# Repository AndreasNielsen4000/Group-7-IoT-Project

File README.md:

# Group 7 IoT Project: Wireless Stereo Speaker System
This one of the two github pages for Group 7s project for DTU course 34346 Networking technologies and application development for the Internet of Things (IoT).
## Group Members
- Andreas Nielsen: s203833
- Alexander Nordentoft: s176361
- Rasmus Kurdahl-Martinsen: s194337
- Sergio Piqueras Moreno: s232104
- Hugo Velasco Bombin: s233845
- Anton Per Rønnedal: s203821

## Project Description

The project is a wireless speaker system that can play music from a Bluetooth or WiFi source. The system consists of four main parts with subcomponents:

1. A speaker with an ESP32-WROOM-32 microcontroller.
   1. Two custom PCBs
      1. A power board with USB-C PD and a battery management system.
      2. An audio board with a class D amplifier, a DAC, ESP32-WROOM-32, and an nRF24L01 module.
      3. Rotary encoder for volume control and switching modes.
      4. OLED display for showing the current mode, metadata, battery level and volume.
2. ESP32 IoT Bridge
   1. An ESP32-WROOM-32 microcontroller.
   2. nRF24L01 module.
3. Azure Backend
    1. WebAPI for managing the speaker system.
    2. Simple front end for controlling the speaker system.
4. Thunkable App
    1. An app for controlling the speaker system using the Azure backend.

## Description of the Speaker System

*Code in BT_I2S_URL_OLED*

The speaker system consists of a speaker with an ESP32-WROOM-32 microcontroller. The speaker is powered by a custom power board with USB-C PD and a battery management system. The speaker can be powered by three 18650 batteries or by USB-C PD. The battery can be charged using USB-C PD.

The audio is played by a custom audio board with a class D amplifier.

The speaker can play music from a Bluetooth or WiFi source. The speaker can be controlled using the Thunkable app, the Azure backend or by using the rotary encoder and OLED display on the speaker.

When powering on the speaker, a byte will be read form the EEPROM to determine the mode of the speaker. The speaker can be in one of the following modes besides being powered off:
WiFi, Bluetooth, Standby or Charge

When powered on, a short press on the rotary encoder will switch betweent the current active mode to the valid passive mode, e.g. if the speaker is in WiFi mode and charging, a short press will switch to Charge mode. A short press again will switch back to WiFi mode. If the device is not charging, the speaker will go into Standby mode instead. From Standby mode, a long press (10 seconds) will turn off the speaker.

In all modes except powered off, the speaker will show the battery level on the OLED display as well as the current mode. It will have an active nRF network to the IoT Bridge and will be able to receive and transmit payloads from the nRF network.

Once a second the speaker checks for any changes in local device parameters and if they are different from the last time the speaker will send a payload to the IoT Bridge with the new parameters. Should the speaker receive a payload from the IoT Bridge, it will parse the payload and act accordingly.

When in WiFi mode, the speaker will start by playing Radio BOB! bby default. The speaker will show the current song and Internet Radio station on the OLED display.

When in Bluetooth mode, the speaker will connect to the last connected Bluetooth device and that device will be able to play music on the speaker. The speaker will show the current song on the OLED display. When connected to a compatible device, the speaker will show the current song on the OLED display and turning the volume down to 0 sends a pause command to the device. Turning the volume up will send a play command to the device.

When in Standby mode, the speaker will not play music, but the ESP32 will still be running with the OLED display and the nRF network active.

When in Charge mode, the speaker will charge the battery and show the battery level on the OLED display.

## Description of the IoT Bridge

*Code in NRF_COM_HUB*

The IoT Bridge consists of an ESP32-WROOM-32 microcontroller and an nRF24L01 module. The IoT Bridge is connected to the Azure backend using WiFi. The IoT Bridge sends a request to the Azure backend 5 second to check for any changes in the data. If the data has changed, the IoT Bridge sends the new data to the speaker system. The IoT Bridge receives data from the speaker system and sends it to the Azure backend.

## Description of the Azure Backend

*Code in https://github.com/AndreasNielsen4000/azureradioapi]https://github.com/AndreasNielsen4000/azureradioapi*

The Azure backend consists of a WebAPI for managing the speaker system. The WebAPI is connected to the IoT Bridge using WiFi. The WebAPI receives data from the IoT Bridge and sends data to the IoT Bridge. The WebAPI has a simple front end for controlling the speaker system.

## Description of the Thunkable App

*The block-code for the app can be found here https://x.thunkable.com/projectPage/65fbfc2f66a304c1d58aabaa*

Using Thunkable an app was created for controlling the speaker system using the Azure backend. The app can be used to change the mode of the speaker system, search for new Internet Radio stations, change Internet Radio station and change the volume.
The app works by using HTTP GET to search and filter Internet Radio URLs and then HTTP POST to the Azure with updated device parameters.

## Overview of Communication

## Video Preview of Functionality
In the following video, the device is powered on from the off-state, going into Bluetooth mode. The rotary encoder is turned up, issuing a play request to the connected iPhone. 
Then the device is switched over to WiFi mode and playing Radio BOB!.

https://github.com/AndreasNielsen4000/Group-7-IoT-Project/assets/8758884/1d90d405-0698-4473-90d2-c6516d68bdfd

## Work Distribution

| Responsibility                | Main                                 | Secondary            |
|-------------------------------|--------------------------------------|----------------------|
| **Mobile App**                | Andreas                              | Alexander            |
| **OLED**                      | Alexander                            | ------               |
| **LEDs**                      | Sergio                               | ------               |
| **PCBs**                      | Anton                                | ------               |
| **Soldering**                 | Anton                                | ------               |
| **3D Design**                 | Sergio                               | Hugo                 |
| **Azure**                     | Rasmus                               | Andreas              |
| **Back-end**                  | Andreas                              | Rasmus               |
| **Front-end**                 | Andreas                              | Alexander            |
| **IoT bridge**                | Rasmus                               | Andreas, Alexander   |
| **nRF**                       | Sergio                               | Rasmus, Andreas      |
| **nRF Network**               | Andreas                              | Alexander, Sergio    |
| **WiFi (mode)**               | Alexander                            | Andreas              |
| **Bluetooth (mode)**          | Alexander                            | Andreas              |
| **EEPROM**                    | Alexander                            | ------               |
| **Battery Reading**           | Rasmus                               | ------               |
| **Power Delivery**            | Anton                                | ------               |
| **BMS**                       | Anton                                | ------               |
| **Rotary encoder**            | Anton & Alexander                    | ------               |
| **State Machine**             | Anton                                | ------               |
| **Code Integration**          | Andreas & Alexander                  | Anton                |
| **Final prototype assembly**  | Alexander, Anton & Sergio            | ------               |
| **Report**                    | All                                  | ------               |
| **Poster**                    | All                                  | ------               |

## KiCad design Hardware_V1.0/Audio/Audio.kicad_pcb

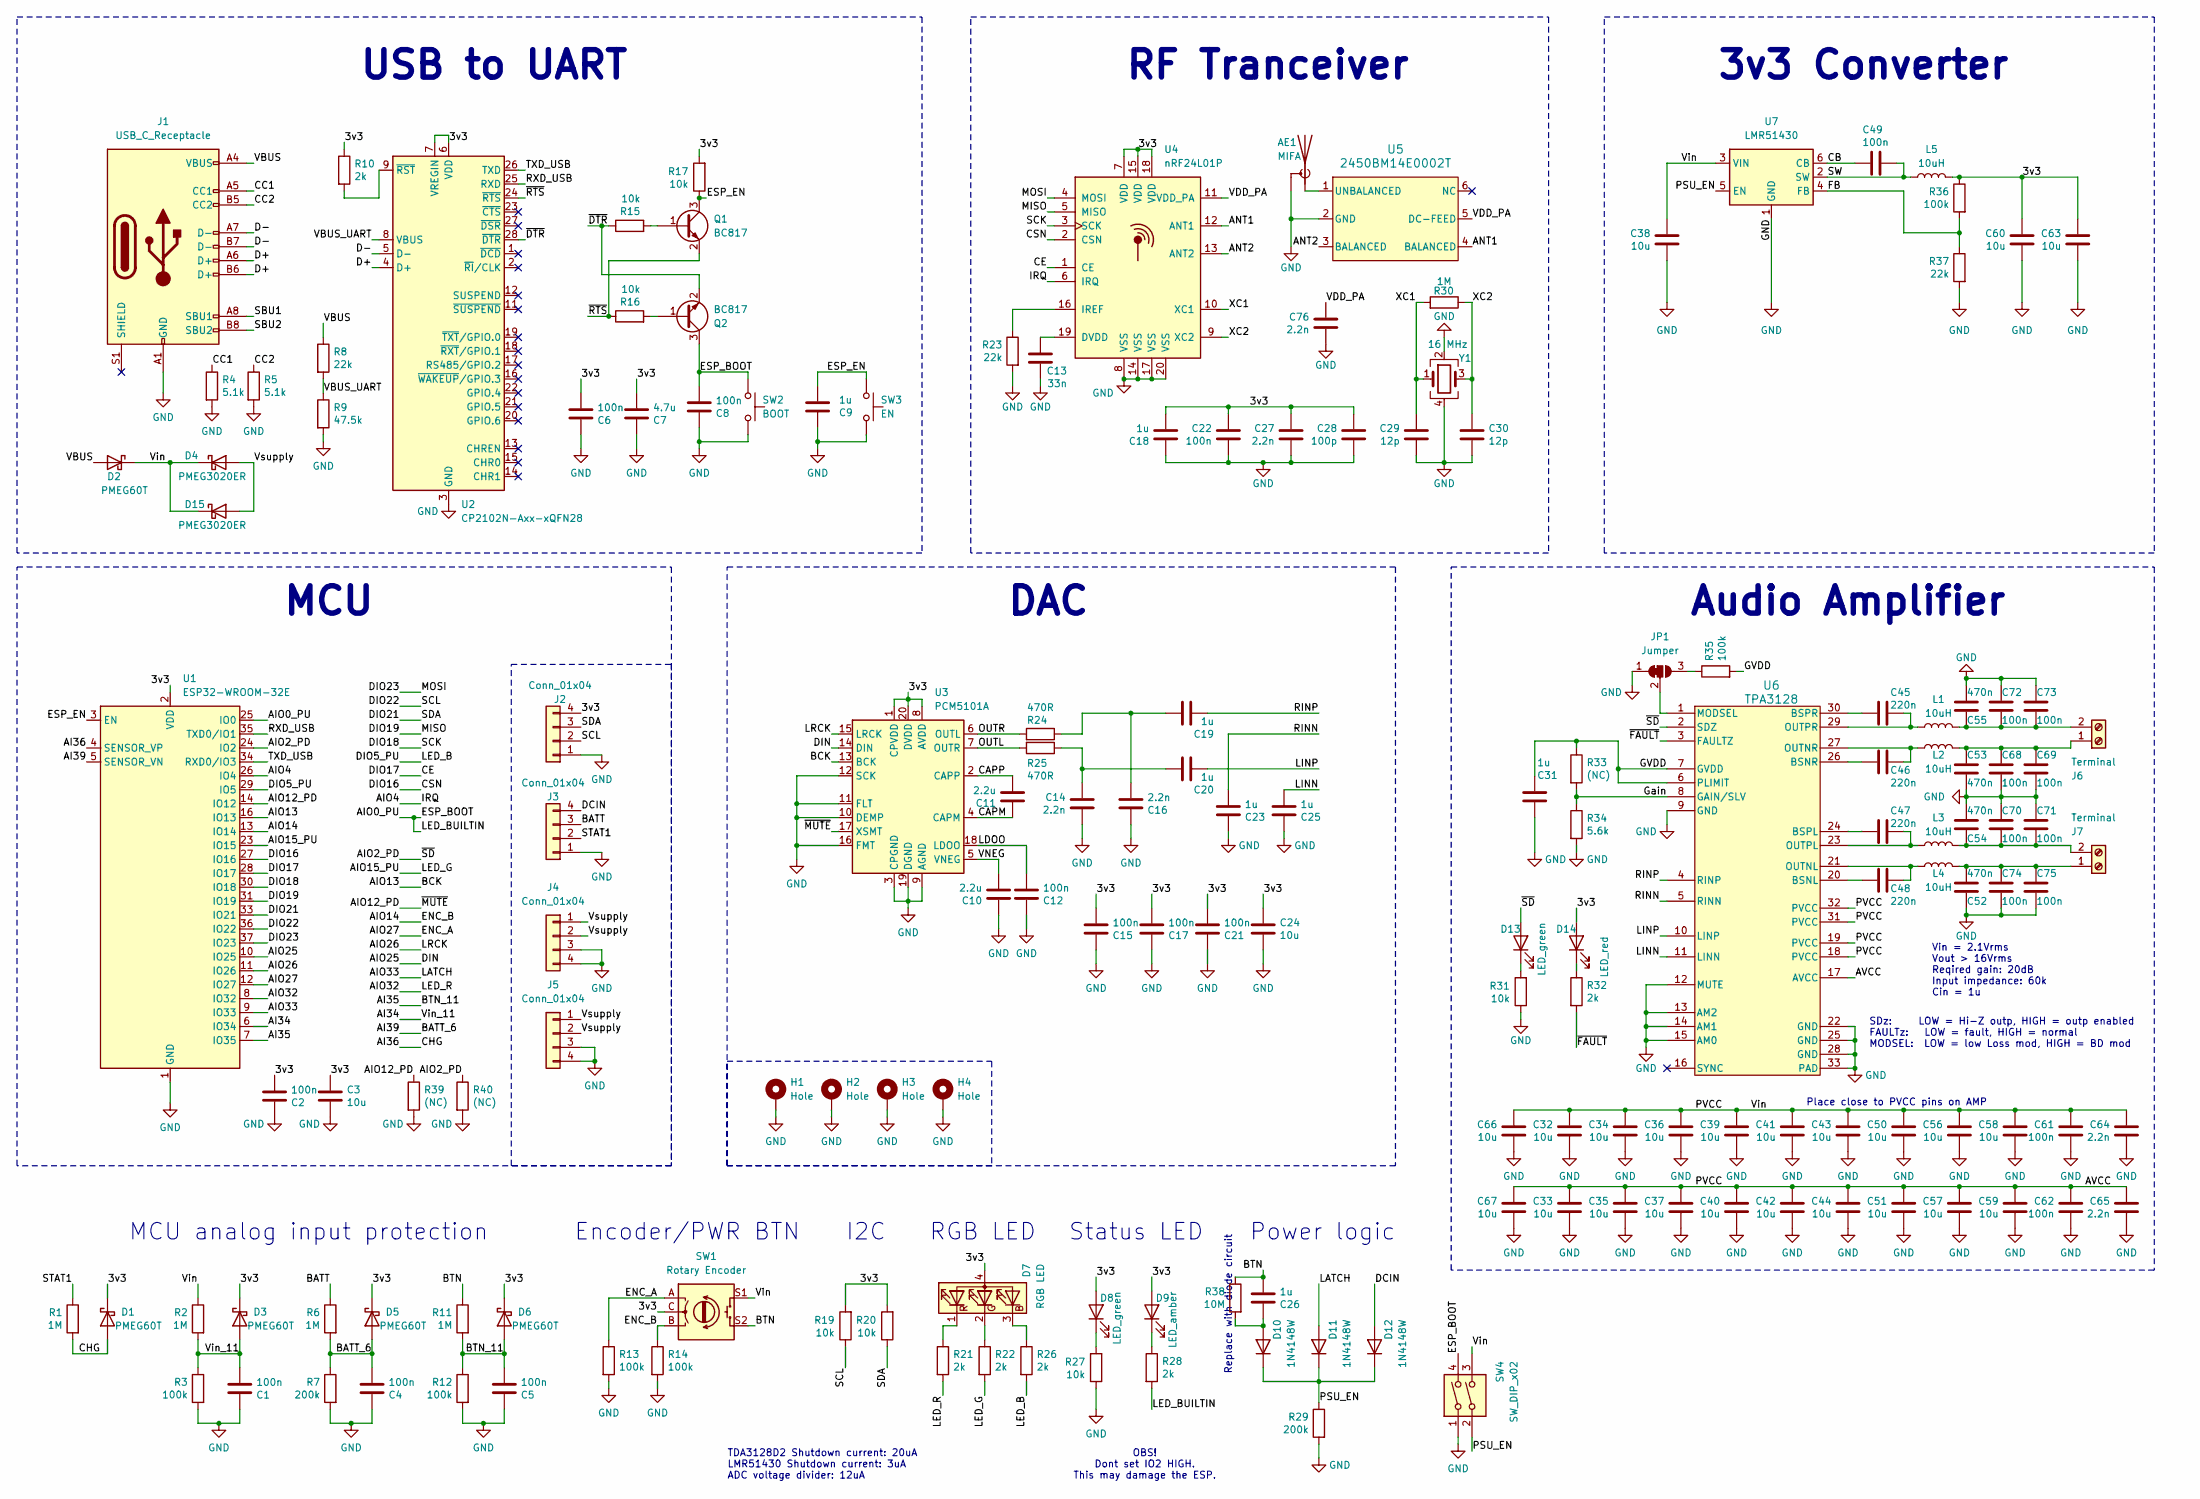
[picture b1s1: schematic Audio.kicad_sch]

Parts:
AE1: MIFA; Texas_SWRA117D_2.4GHz_Right
C1, C2, C4, C5, C6, C8, C12, C15, C17, C21, C22, C49, C61, C62, C68, C69, C70, C71, C72, C73, C74, C75: 100n; C_0603_1608Metric_Pad1.08x0.95mm_HandSolder; MPN CL10B104JB8NNNC
C3, C24, C32, C33, C34, C35, C36, C37, C38, C39, C40, C41, C42, C43, C44, C50, C51, C56, C57, C58, C59, C60, C63, C66, C67: 10u; C_1206_3216Metric_Pad1.33x1.80mm_HandSolder; MPN CL31B106KBHNNNE
C7: 4.7u; C_0603_1608Metric_Pad1.08x0.95mm_HandSolder; MPN GRM188R6YA475KE15J
C9, C18, C19, C20, C23, C25, C26, C31: 1u; C_0603_1608Metric_Pad1.08x0.95mm_HandSolder; MPN CL10A105KB8NNNC
C10, C11: 2.2u; C_0603_1608Metric_Pad1.08x0.95mm_HandSolder; MPN CL10A225KP8NNNC
C13: 33n; C_0603_1608Metric_Pad1.08x0.95mm_HandSolder; MPN CL10B333KB8NNNC
C14, C16, C27, C64, C65, C76: 2.2n; C_0603_1608Metric_Pad1.08x0.95mm_HandSolder; MPN CL10B222KB8NNND
C28: 100p; C_0603_1608Metric_Pad1.08x0.95mm_HandSolder; MPN CL10C101JB8NNND
C29, C30: 12p; C_0603_1608Metric_Pad1.08x0.95mm_HandSolder; MPN CL10C120JB8NNNC
C45, C46, C47, C48: 220n; C_0603_1608Metric_Pad1.08x0.95mm_HandSolder; MPN CL10B224KB8NNNC
C52, C53, C54, C55: 470n; C_0805_2012Metric_Pad1.18x1.45mm_HandSolder; MPN CL21B474KBFNNNE
D1, D2, D3, D5, D6: PMEG60T; Nexperia_CFP3_SOD-123W; MPN PMEG60T30ELRX
D4, D15: PMEG3020ER; Nexperia_CFP3_SOD-123W; MPN PMEG3020ER,115
D7: RGB LED; RGB_LED
D8, D13: LED_green; LED_0603_1608Metric_Pad1.05x0.95mm_HandSolder; MPN 150060GS75000
D9: LED_amber; LED_0603_1608Metric_Pad1.05x0.95mm_HandSolder; MPN 150060YS75000
D10, D11, D12: 1N4148W; D_SOD-123
D14: LED_red; LED_0603_1608Metric_Pad1.05x0.95mm_HandSolder; MPN 150060RS75000
H1, H2, H3, H4: Hole; MountingHole_3.2mm_M3_DIN965_Pad
J1: USB_C_Receptacle; USB_C_Receptacle_GCT_USB4105-xx-A_16P_TopMnt_Horizontal; MPN USB4105-GF-A-120
J2, J3, J4, J5: Conn_01x04; PinSocket_1x04_P2.54mm_Vertical
J6, J7: Terminal; TerminalBlock_bornier-2_P5.08mm
JP1: Jumper; SolderJumper-3_P1.3mm_Bridged12_RoundedPad1.0x1.5mm
L1, L2, L3, L4, L5: 10uH; 1274AS; MPN DD1274AS-H-100M=P3
Q1, Q2: BC817; SOT-23; MPN BC817-QR
R1, R2, R6, R11, R30: 1M; R_0603_1608Metric_Pad0.98x0.95mm_HandSolder; MPN CRCW06031M00FKEC
R3, R12, R13, R14, R35, R36: 100k; R_0603_1608Metric_Pad0.98x0.95mm_HandSolder; MPN CRCW0603100KFKEA
R4, R5: 5.1k; R_0603_1608Metric_Pad0.98x0.95mm_HandSolder; MPN CRCW06035K10FKEA
R7, R29: 200k; R_0603_1608Metric_Pad0.98x0.95mm_HandSolder; MPN CRCW0603200KFKEA
R8, R23, R37: 22k; R_0603_1608Metric_Pad0.98x0.95mm_HandSolder; MPN CRCW060322K0FKEA
R9: 47.5k; R_0603_1608Metric_Pad0.98x0.95mm_HandSolder; MPN CRCW060347K5FKEA
R10, R21, R22, R26, R28, R32: 2k; R_0603_1608Metric_Pad0.98x0.95mm_HandSolder; MPN CRCW06032K00FKEC
R15, R16, R17, R19, R20, R27, R31: 10k; R_0603_1608Metric_Pad0.98x0.95mm_HandSolder; MPN CRCW060310K0FKEC
R24, R25: 470R; R_0603_1608Metric_Pad0.98x0.95mm_HandSolder; MPN CRCW0603470RFKEA
R33, R39, R40: (NC); R_0603_1608Metric_Pad0.98x0.95mm_HandSolder
R34: 5.6k; R_0603_1608Metric_Pad0.98x0.95mm_HandSolder; MPN CRCW06035K60FKEA
R38: 10M; R_0603_1608Metric_Pad0.98x0.95mm_HandSolder; MPN CRCW060310M0FKEC
SW1: Rotary Encoder; EC11_RotaryEncoder
SW2: BOOT; EVQPUK; MPN EVQ-PUK02K
SW3: EN; EVQPUK; MPN EVQ-PUK02K
SW4: SW_DIP_x02; SW_DIP_SPSTx02_Slide_6.7x6.64mm_W8.61mm_P2.54mm_LowProfile; MPN 219-2MST
U1: ESP32-WROOM-32E; ESP32-WROOM-32D; MPN ESP32-WROOM-32E-N16
U2: CP2102N-Axx-xQFN28; QFN-28-1EP_5x5mm_P0.5mm_EP3.35x3.35mm; MPN CP2102N-A02-GQFN28
U3: PCM5101A; TSSOP-20_4.4x6.5mm_P0.65mm; MPN PCM5101AQPWRQ1
U4: nRF24L01P; QFN-20-1EP_4x4mm_P0.5mm_EP2.5x2.5mm; MPN nRF24L01P
U5: 2450BM14E0002T; 2450BM14E0003T_JOT-L; MPN 2450BM14A0002T
U6: TPA3128; DAP32_4P36X4P11_TEX; MPN TPA3128D2DAPR
U7: LMR51430; SOT-23-6; MPN LMR51430YDDCR
Y1: 16 MHz; Crystal_SMD_2520-4Pin_2.5x2.0mm; MPN ECS-160-10-36-CKM-TR3

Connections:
/3v3: C2.2, C3.1, C6.2, C7.2, C15.2, C17.2, C18.2, C21.2, C22.1, C24.1, C27.1, C28.1, C60.1, C63.1, D1.1 (K), D3.1 (K), D5.1 (K), D6.1 (K), D7.4 (A), D8.2 (A), D9.2 (A), D14.2 (A), J2.4, L5.2, R10.1, R17.2, R19.2, R20.2, R36.1, SW1.C, U1.2 (VDD), U2.6 (VDD), U2.7 (VREGIN), U3.1 (CPVDD), U3.8 (AVDD), U3.20 (DVDD), U4.7 (VDD), U4.15 (VDD), U4.18 (VDD)
/AI34: C1.2, D3.2 (A), R2.2, R3.1, U1.6 (IO34)
/AI35: C5.2, D6.2 (A), R11.2, R12.1, U1.7 (IO35)
/AI36: D1.2 (A), R1.2, U1.4 (SENSOR_VP)
/AI39: C4.2, D5.2 (A), R6.2, R7.1, U1.5 (SENSOR_VN)
/AIO0_PU: C8.2, Q2.3 (C), R28.2, SW2.1, SW4.4, U1.25 (IO0)
/AIO2_PD: D13.2 (A), R40.1, U1.24 (IO2), U6.2 (SDZ)
/AIO4: U1.26 (IO4), U4.6 (IRQ)
/AIO12_PD: R39.1, U1.14 (IO12), U3.17 (XSMT)
/AIO13: U1.16 (IO13), U3.13 (BCK)
/AIO14: R14.1, SW1.B, U1.13 (IO14)
/AIO15_PU: R22.2, U1.23 (IO15)
/AIO25: U1.10 (IO25), U3.14 (DIN)
/AIO26: U1.11 (IO26), U3.15 (LRCK)
/AIO27: R13.1, SW1.A, U1.12 (IO27)
/AIO32: R21.2, U1.8 (IO32)
/AIO33: D11.2 (A), U1.9 (IO33)
/ANT1: U4.12 (ANT1), U5.4 (BALANCED)
/ANT2: U4.13 (ANT2), U5.3 (BALANCED)
/AVCC: C32.1, C33.1, C34.1, C35.1, C36.1, C37.1, C38.1, C39.1, C40.1, C41.1, C42.1, C43.1, C44.1, C50.1, C51.1, C56.1, C57.1, C58.1, C59.1, C61.1, C62.1, C64.1, C65.1, C66.1, C67.1, D2.1 (K), D4.1 (K), D15.1 (K), R2.1, SW1.S1, SW4.3, U6.17 (AVCC), U6.18 (PVCC), U6.19 (PVCC), U6.31 (PVCC), U6.32 (PVCC), U7.3 (VIN)
/BATT: J3.3, R6.1
/BTN: C26.2, R11.1, R38.1, SW1.S2
/CAPM: C11.1, U3.4 (CAPM)
/CAPP: C11.2, U3.2 (CAPP)
/CB: C49.2, U7.6 (CB)
/CC1: J1.A5 (CC1), R4.1
/CC2: J1.B5 (CC2), R5.1
/CE: U1.28 (IO17), U4.1 (CE)
/CSN: U1.27 (IO16), U4.2 (CSN)
/D+: J1.A6 (D+), J1.B6 (D+), U2.4 (D+)
/D-: J1.A7 (D-), J1.B7 (D-), U2.5 (D-)
/DCIN: D12.2 (A), J3.4
/DIO5_PU: R26.2, U1.29 (IO5)
/DIO18: U1.30 (IO18), U4.3 (SCK)
/DIO19: U1.31 (IO19), U4.5 (MISO)
/DIO21: J2.3, R20.1, U1.33 (IO21)
/DIO22: J2.2, R19.1, U1.36 (IO22)
/DIO23: U1.37 (IO23), U4.4 (MOSI)
/ESP_EN: C9.2, Q1.3 (C), R17.1, SW3.1, U1.3 (EN)
/FB: R36.2, R37.1, U7.4 (FB)
/GVDD: C31.2, R33.1, R35.2, U6.6 (PLIMIT), U6.7 (GVDD)
/Gain: R33.2, R34.1, U6.8 (GAIN/SLV)
/LDOO: C12.2, U3.18 (LDOO)
/LINN: C25.2, U6.11 (LINN)
/LINP: C20.2, U6.10 (LINP)
/OUTL: R25.2, U3.7 (OUTR)
/OUTR: R24.2, U3.6 (OUTL)
/PSU_EN: D10.1 (K), D11.1 (K), D12.1 (K), R29.1, SW4.2, U7.5 (EN)
/RINN: C23.2, U6.5 (RINN)
/RINP: C19.2, U6.4 (RINP)
/RXD_USB: U1.35 (TXD0/IO1), U2.25 (RXD)
/SBU1: J1.A8 (SBU1)
/SBU2: J1.B8 (SBU2)
/STAT1: J3.2, R1.1
/SW: C49.1, L5.1, U7.2 (SW)
/TXD_USB: U1.34 (RXD0/IO3), U2.26 (TXD)
/VBUS: D2.2 (A), J1.A4 (VBUS), J1.A9 (VBUS), J1.B4 (VBUS), J1.B9 (VBUS), R8.1
/VBUS_UART: R8.2, R9.1, U2.8 (VBUS)
/VDD_PA: C76.1, U4.11 (VDD_PA), U5.5 (DC-FEED)
/VNEG: C10.2, U3.5 (VNEG)
/Vsupply: D4.2 (A), D15.2 (A), J4.1, J4.2, J5.1, J5.2
/XC1: C29.1, R30.2, U4.10 (XC1), Y1.1
/XC2: C30.1, R30.1, U4.9 (XC2), Y1.3
/~DTR: Q2.2 (E), R15.1, U2.28 (~DTR)
/~FAULT: R32.2, U6.3 (FAULTZ)
/~RTS: Q1.2 (E), R16.1, U2.24 (~RTS)
GND: AE1.2 (Shield), C1.1, C2.1, C3.2, C4.1, C5.1, C6.1, C7.1, C8.1, C9.1, C10.1, C12.1, C13.2, C14.2, C15.1, C16.1, C17.1, C18.1, C21.1, C22.2, C23.1, C24.2, C25.1, C27.2, C28.2, C29.2, C30.2, C31.1, C32.2, C33.2, C34.2, C35.2, C36.2, C37.2, C38.2, C39.2, C40.2, C41.2, C42.2, C43.2, C44.2, C50.2, C51.2, C52.1, C53.1, C54.2, C55.2, C56.2, C57.2, C58.2, C59.2, C60.2, C61.2, C62.2, C63.2, C64.2, C65.2, C66.2, C67.2, C68.1, C69.1, C70.2, C71.2, C72.2, C73.2, C74.1, C75.1, C76.2, H1.1, H2.1, H3.1, H4.1, J1.A1 (GND), J1.A12 (GND), J1.B1 (GND), J1.B12 (GND), J2.1, J3.1, J4.3, J4.4, J5.3, J5.4, JP1.1 (A), R3.2, R4.2, R5.2, R7.2, R9.2, R12.2, R13.2, R14.2, R23.2, R27.1, R29.2, R31.1, R34.2, R37.2, R39.2, R40.2, SW2.2, SW3.2, SW4.1, U1.1 (GND), U1.15 (GND), U1.38 (GND), U1.39 (GND), U2.3 (GND), U2.29 (GND), U3.3 (CPGND), U3.9 (AGND), U3.10 (DEMP), U3.11 (FLT), U3.12 (SCK), U3.16 (FMT), U3.19 (DGND), U4.8 (VSS), U4.14 (VSS), U4.17 (VSS), U4.20 (VSS), U5.2 (GND), U6.9 (GND), U6.12 (MUTE), U6.13 (AM2), U6.14 (AM1), U6.15 (AM0), U6.22 (GND), U6.25 (GND), U6.28 (GND), U6.33 (PAD), U7.1 (GND), Y1.2, Y1.4
unnamed: AE1.1 (A), U5.1 (UNBALANCED)
unnamed: C14.1, C20.1, R25.1
unnamed: C16.2, C19.1, R24.1
unnamed: D7.3 (BK), R26.1
unnamed: D7.2 (GK), R22.1
unnamed: D7.1 (RK), R21.1
unnamed: D8.1 (K), R27.2
unnamed: D9.1 (K), R28.1
unnamed: C26.1, D10.2 (A), R38.2
unnamed: D13.1 (K), R31.2
unnamed: D14.1 (K), R32.1
unnamed: C53.2, C68.2, C69.2, J6.1, L2.1
unnamed: C55.1, C72.1, C73.1, J6.2, L1.2
unnamed: C52.2, C74.2, C75.2, J7.1, L4.1
unnamed: C54.1, C70.1, C71.1, J7.2, L3.2
unnamed: JP1.3 (B), R35.1
unnamed: JP1.2 (C), U6.1 (MODSEL)
unnamed: Q1.1 (B), R15.2
unnamed: Q2.1 (B), R16.2
unnamed: R10.2, U2.9 (~RST)
unnamed: C13.1, U4.19 (DVDD)
unnamed: R23.1, U4.16 (IREF)
unnamed: C48.2, U6.20 (BSNL)
unnamed: C46.2, U6.26 (BSNR)
unnamed: C47.2, U6.24 (BSPL)
unnamed: C45.2, U6.30 (BSPR)
unnamed: C48.1, L4.2, U6.21 (OUTNL)
unnamed: C46.1, L2.2, U6.27 (OUTNR)
unnamed: C47.1, L3.1, U6.23 (OUTPL)
unnamed: C45.1, L1.1, U6.29 (OUTPR)

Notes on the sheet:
TDA3128D2 Shutdown current: 20uA LMR51430 Shutdown current: 3uA ADC voltage divider: 12uA
Audio Amplifier
I2C
Vin = 2.1Vrms Vout > 16Vrms Reqired gain: 20dB Input impedance: 60k Cin = 1u
RGB LED
MCU
Power logic
Place close to PVCC pins on AMP
DAC
OBS! Dont set IO2 HIGH. This may damage the ESP.
Status LED
MCU analog input protection
USB to UART
RF Tranceiver
Replace with diode circuit
Encoder/PWR BTN
3v3 Converter
SDz: LOW = Hi-Z outp, HIGH = outp enabled FAULTz: LOW = fault, HIGH = normal MODSEL: LOW = low Loss mod, HIGH = BD mod

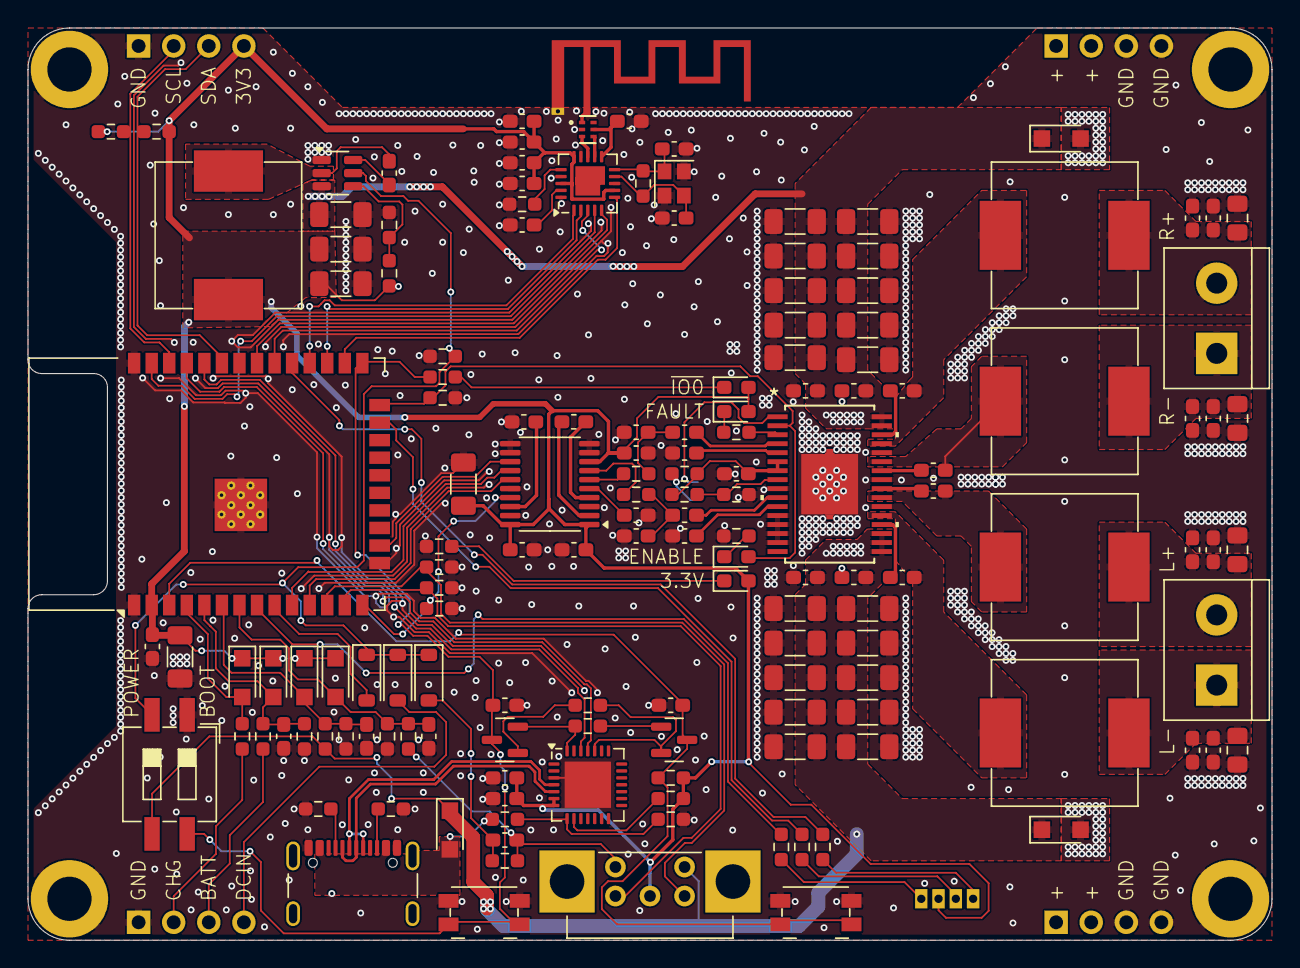
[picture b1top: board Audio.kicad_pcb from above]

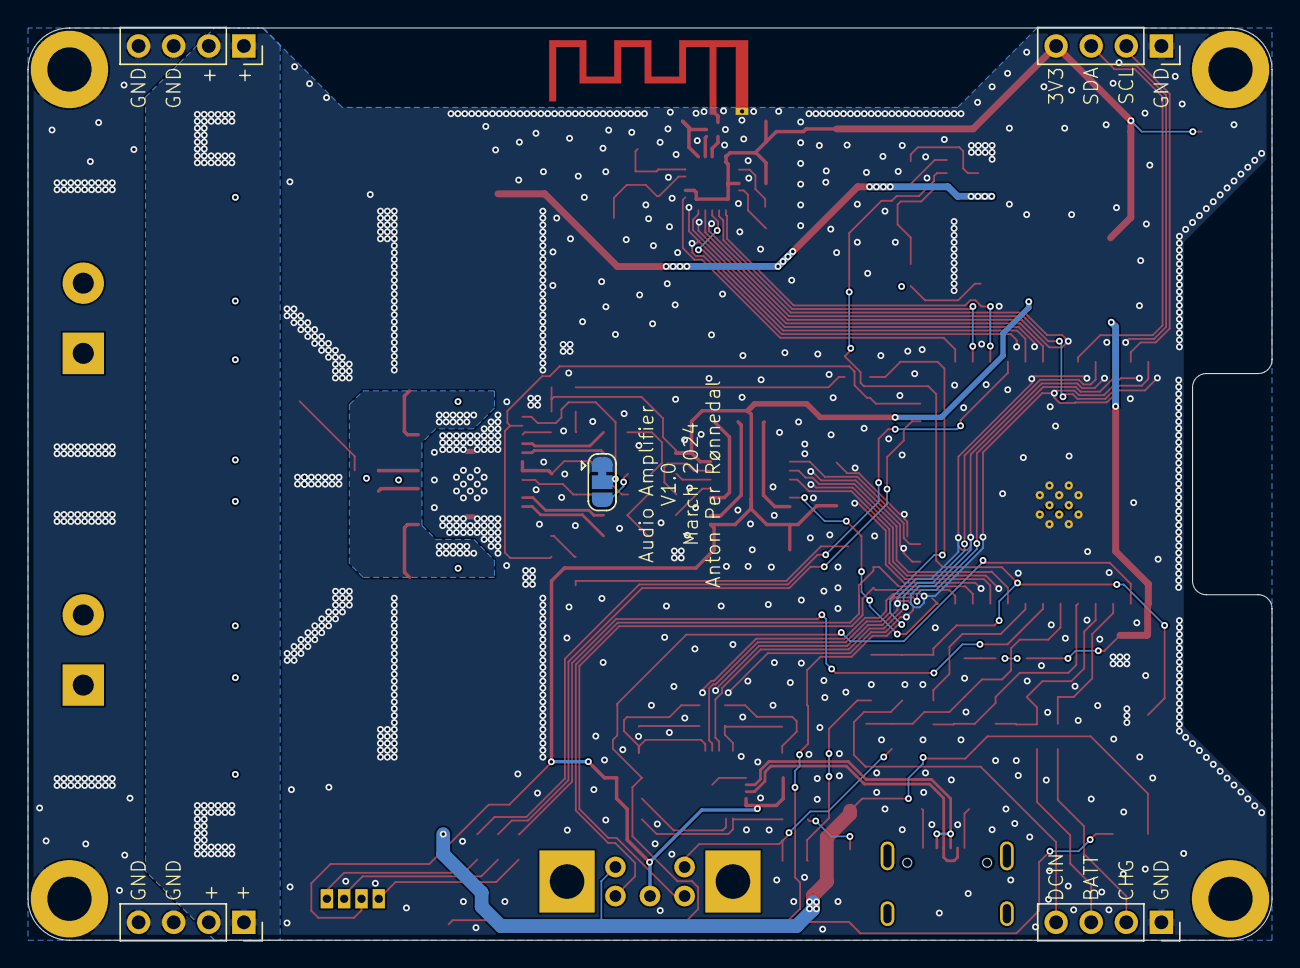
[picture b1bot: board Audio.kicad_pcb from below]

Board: 4 copper layers, 90.0 x 66.0 mm, 162 parts (5 on the bottom side), 95 nets.

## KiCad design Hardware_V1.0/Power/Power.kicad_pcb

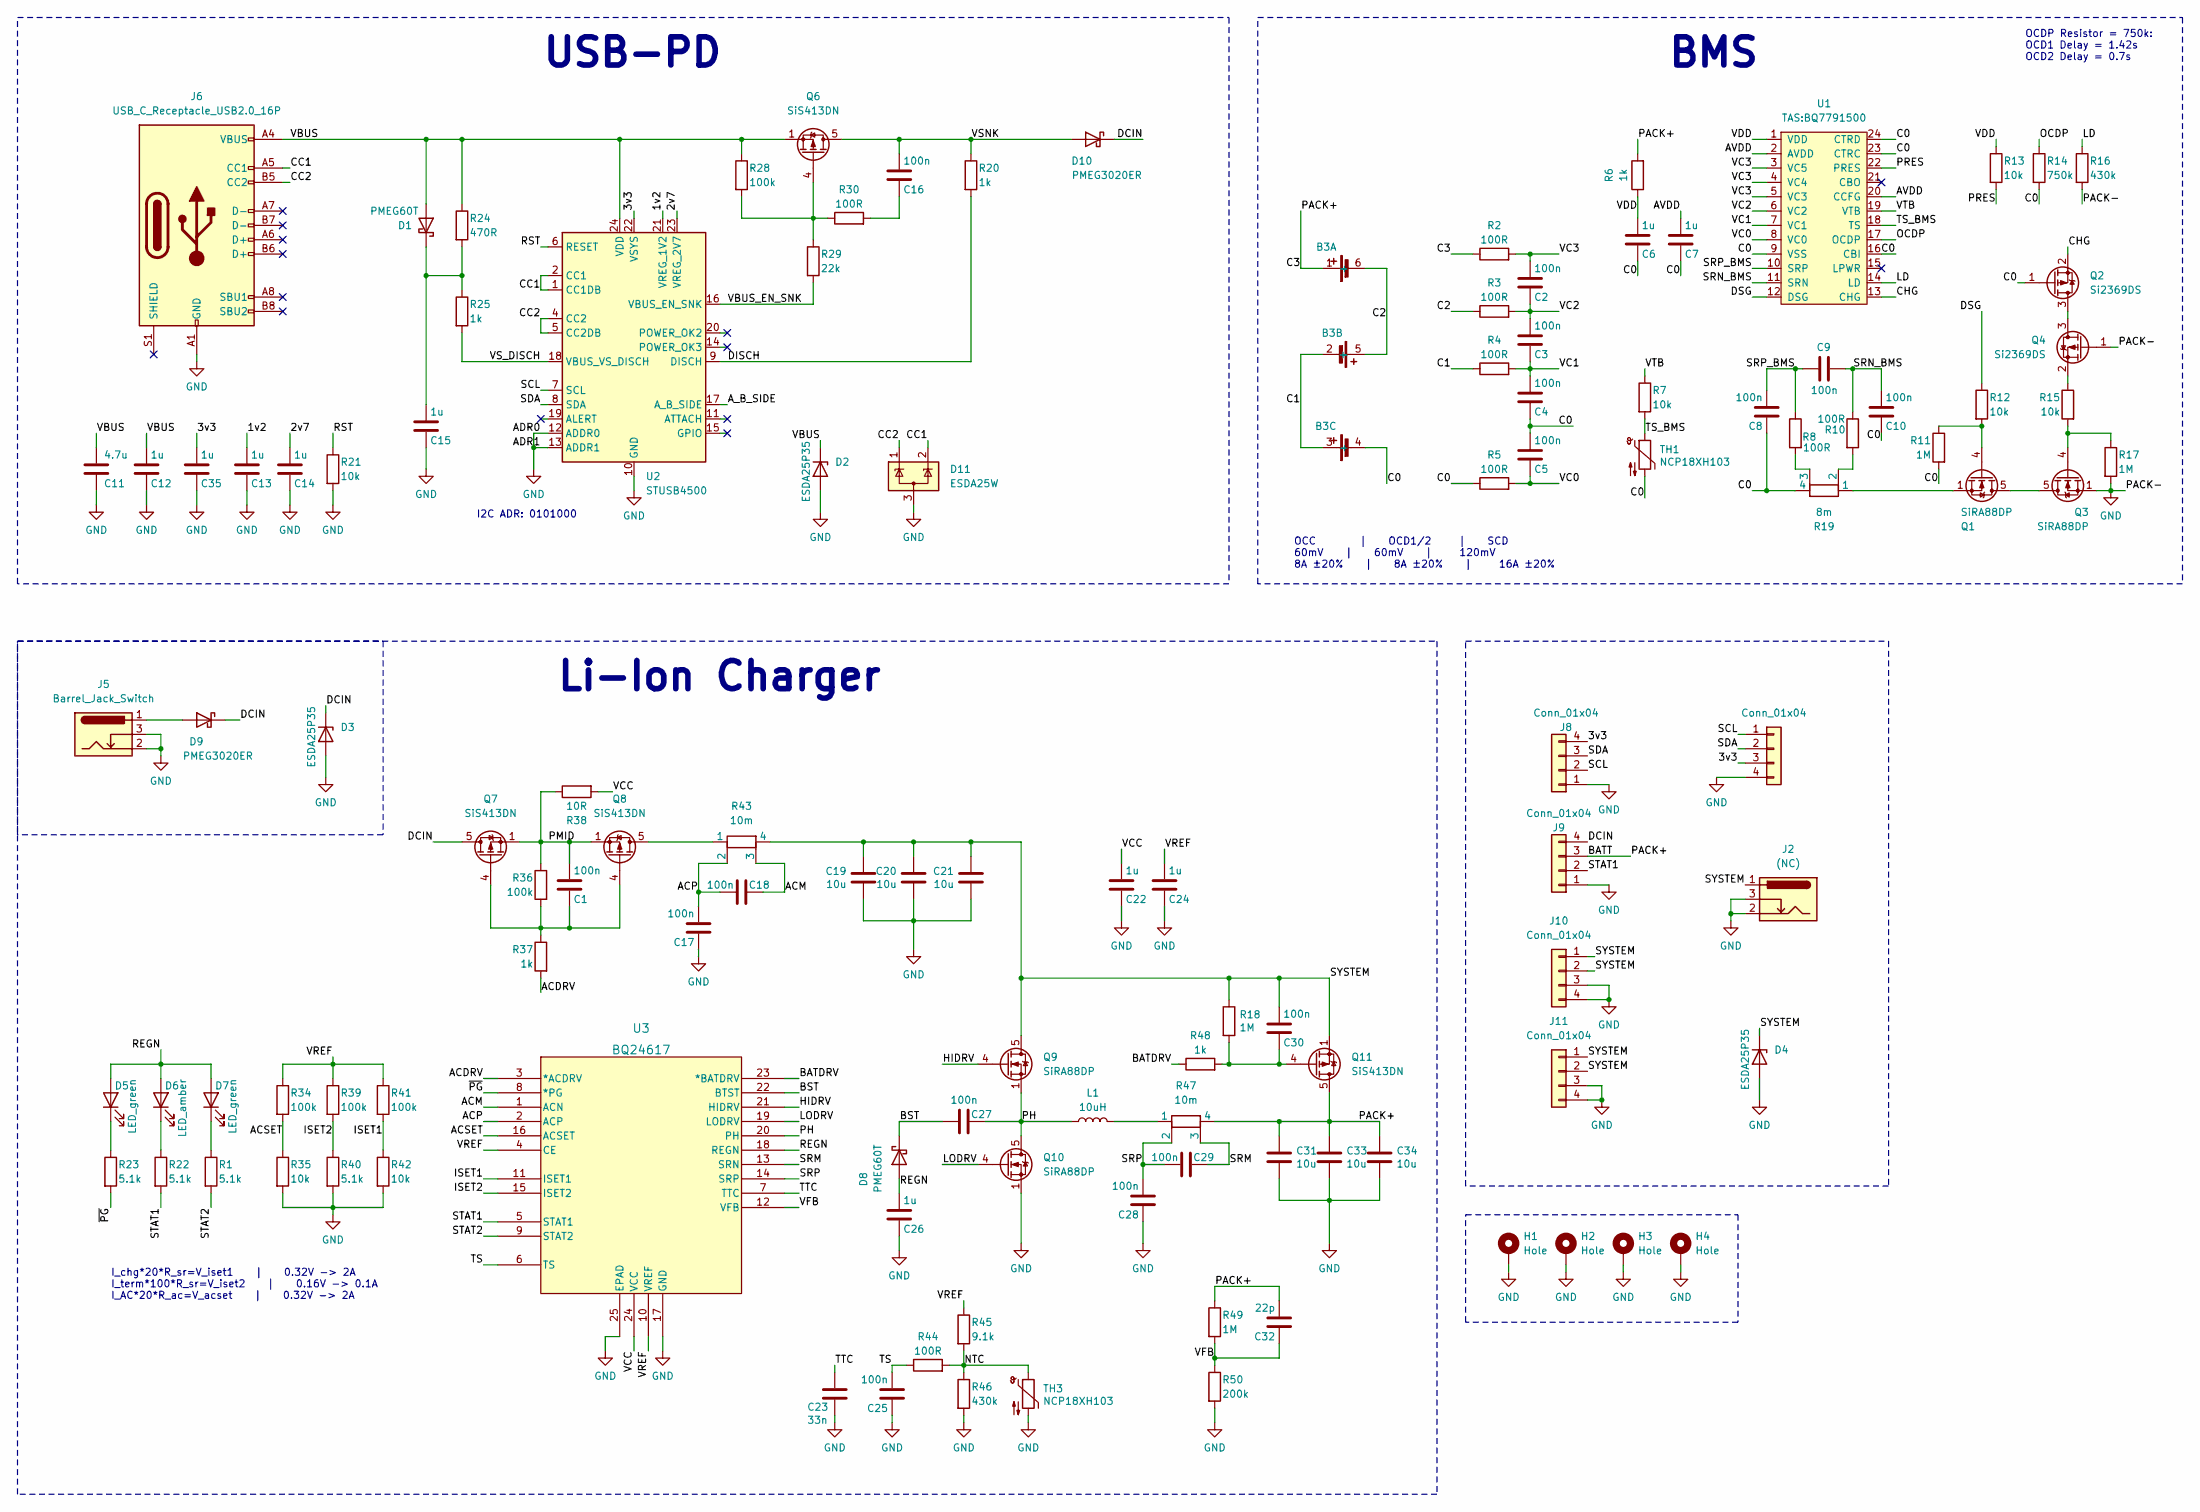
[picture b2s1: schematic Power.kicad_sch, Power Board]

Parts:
B3: BLM_18650x3
C1, C2, C3, C4, C5, C8, C9, C10, C16, C17, C18, C25, C27, C28, C29, C30: 100n; C_0603_1608Metric_Pad1.08x0.95mm_HandSolder; MPN CL10B104JB8NNNC
C6, C7, C12, C13, C14, C15, C22, C24, C26, C35: 1u; C_0603_1608Metric_Pad1.08x0.95mm_HandSolder; MPN CL10A105KB8NNNC
C11: 4.7u; C_0603_1608Metric_Pad1.08x0.95mm_HandSolder; MPN GRM188R6YA475KE15J
C19, C20, C21, C31, C33, C34: 10u; C_1206_3216Metric_Pad1.33x1.80mm_HandSolder; MPN CL31B106KBHNNNE
C23: 33n; C_0603_1608Metric_Pad1.08x0.95mm_HandSolder; MPN CL10B333KB8NNNC
C32: 22p; C_0603_1608Metric_Pad1.08x0.95mm_HandSolder; MPN CL10C220JB8NNNC
D1, D8: PMEG60T; Nexperia_CFP3_SOD-123W; MPN PMEG60T30ELRX
D2, D3, D4: ESDA25P35; QFN1610_STM-L; MPN ESDA25P35-1U1M
D5, D7: LED_green; LED_0603_1608Metric_Pad1.05x0.95mm_HandSolder; MPN 150060GS75000
D6: LED_amber; LED_0603_1608Metric_Pad1.05x0.95mm_HandSolder; MPN 150060YS75000
D9, D10: PMEG3020ER; Nexperia_CFP3_SOD-123W; MPN PMEG3020ER,115
D11: ESDA25W; SOT-323_SC-70_Handsoldering; MPN ESDA25W
H1, H2, H3, H4: Hole; MountingHole_3.2mm_M3_DIN965_Pad
J1: Conn_01x04; JST_PH_S4B-PH-SM4-TB_1x04-1MP_P2.00mm_Horizontal; MPN 4392
J2: (NC); BarrelJack_Wuerth_694106106102_2.0x5.5mm; MPN 694106106102
J5: Barrel_Jack_Switch; BarrelJack_Wuerth_694106106102_2.0x5.5mm; MPN 694106106102
J6: USB_C_Receptacle_USB2.0_16P; USB_C_Receptacle_GCT_USB4105-xx-A_16P_TopMnt_Horizontal; MPN USB4105-GF-A-120
J8, J9, J10, J11: Conn_01x04; PinSocket_1x04_P2.54mm_Vertical
L1: 10uH; 1274AS; MPN DD1274AS-H-100M=P3
Q1, Q3, Q9, Q10: SiRA88DP; PowerPAK_SO-8_Single; MPN SIRA88DP-T1-GE3
Q2, Q4: Si2369DS; SOT-23; MPN SI2369DS-T1-GE3
Q6, Q7, Q8, Q11: SiS413DN; Vishay_PowerPAK_1212-8_Single; MPN SIS413DN-T1-GE3
R1, R22, R23, R40: 5.1k; R_0603_1608Metric_Pad0.98x0.95mm_HandSolder; MPN CRCW06035K10FKEA
R2, R3, R4, R5, R8, R10, R30, R44: 100R; R_0603_1608Metric_Pad0.98x0.95mm_HandSolder; MPN CRCW0603100RFKEC
R6, R20, R25, R37, R48: 1k; R_0603_1608Metric_Pad0.98x0.95mm_HandSolder; MPN CRCW06031K00FKEC
R7, R12, R13, R15, R21, R35, R42: 10k; R_0603_1608Metric_Pad0.98x0.95mm_HandSolder; MPN CRCW060310K0FKEC
R11, R17, R18, R49: 1M; R_0603_1608Metric_Pad0.98x0.95mm_HandSolder; MPN CRCW06031M00FKEC
R14: 750k; R_0603_1608Metric_Pad0.98x0.95mm_HandSolder; MPN CRCW0603750KFKEA
R16, R46: 430k; R_0603_1608Metric_Pad0.98x0.95mm_HandSolder; MPN CRCW0603430KFKEA
R19: 8m; SenseResistor_1206; MPN MSMA1206R0080FCM
R24: 470R; R_0603_1608Metric_Pad0.98x0.95mm_HandSolder; MPN CRCW0603470RFKEC
R28, R34, R36, R39, R41: 100k; R_0603_1608Metric_Pad0.98x0.95mm_HandSolder; MPN CRCW0603100KFKEA
R29: 22k; R_0603_1608Metric_Pad0.98x0.95mm_HandSolder; MPN CRCW060322K0FKEA
R38: 10R; R_0603_1608Metric_Pad0.98x0.95mm_HandSolder; MPN CRCW060310R0FKEC
R43, R47: 10m; SenseResistor_1206; MPN MFSA1206R0100FCM
R45: 9.1k; R_0603_1608Metric_Pad0.98x0.95mm_HandSolder; MPN CRCW06039K10FKEA
R50: 200k; R_0603_1608Metric_Pad0.98x0.95mm_HandSolder; MPN CRCW0603200KFKEA
TH1, TH3: NCP18XH103; R_0603_1608Metric_Pad0.98x0.95mm_HandSolder; MPN NCP18XH103F03RB
U1: TAS:BQ7791500; TSSOP-24_4.4x7.8mm_P0.65mm; MPN BQ7791500PWR
U2: STUSB4500; QFN-24-1EP_4x4mm_P0.5mm_EP2.7x2.7mm; MPN STUSB4500QTR
U3: BQ24617; QFN-24-1EP_4x4mm_P0.5mm_EP2.15x2.15mm_ThermalVias; MPN BQ24617RGER

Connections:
/1v2: C13.1, U2.21 (VREG_1V2)
/2v7: C14.1, U2.23 (VREG_2V7)
/3v3: C35.1, J1.3, J8.4, U2.22 (VSYS)
/ACDRV: R37.2, U3.3 (*ACDRV)
/ACM: C18.2, R43.3, U3.1 (ACN)
/ACP: C17.1, C18.1, R43.2, U3.2 (ACP)
/ACSET: R34.2, R35.1, U3.16 (ACSET)
/AVDD: C7.1, U1.2 (AVDD), U1.20 (CCFG)
/A_B_SIDE: U2.17 (A_B_SIDE)
/BATDRV: R48.1, U3.23 (*BATDRV)
/BATT: B3.1 (+), C31.1, C32.1, C33.1, C34.1, J9.3, Q11.5 (D), R2.1, R6.2, R47.4, R49.1
/BST: C27.1, D8.1 (K), U3.22 (BTST)
/C0: B3.4 (-), C4.2, C5.1, C6.2, C7.2, C8.2, C10.2, Q2.1 (G), R5.1, R11.2, R14.2, R19.4, TH1.2, U1.9 (VSS), U1.16 (CBI), U1.23 (CTRC), U1.24 (CTRD)
/C1: B3.2 (-), B3.3 (+), R4.1
/C2: B3.5 (+), B3.6 (-), R3.1
/CC1: D11.2 (K), J6.A5 (CC1), U2.1 (CC1DB), U2.2 (CC1)
/CC2: D11.1 (K), J6.B5 (CC2), U2.4 (CC2), U2.5 (CC2DB)
/CHG: Q2.2 (S), U1.13 (CHG)
/DCIN: D3.1 (K), D9.1 (K), D10.1 (K), J9.4, Q7.5 (D)
/DISCH: R20.2, U2.9 (DISCH)
/DSG: R12.1, U1.12 (DSG)
/HIDRV: Q9.4 (G), U3.21 (HIDRV)
/ISET1: R41.2, R42.1, U3.11 (ISET1)
/ISET2: R39.2, R40.1, U3.15 (ISET2)
/LD: R16.1, U1.14 (LD)
/LODRV: Q10.4 (G), U3.19 (LODRV)
/NTC: R44.2, R45.2, R46.1, TH3.1
/OCDP: R14.1, U1.17 (OCDP)
/PH: C27.2, L1.2, Q9.1 (S), Q9.2 (S), Q9.3 (S), Q10.5 (D), U3.20 (PH)
/PMID: C1.1, Q7.1 (S), Q7.2 (S), Q7.3 (S), Q8.1 (S), Q8.2 (S), Q8.3 (S), R36.1, R38.1
/PRES: R13.2, U1.22 (PRES)
/REGN: C26.1, D5.2 (A), D6.2 (A), D7.2 (A), D8.2 (A), U3.18 (REGN)
/RST: R21.1, U2.6 (RESET)
/SCL: J1.1, J8.2, U2.7 (SCL)
/SDA: J1.2, J8.3, U2.8 (SDA)
/SRM: C29.2, R47.3, U3.13 (SRN)
/SRN_BMS: C9.2, C10.1, R10.1, U1.11 (SRN)
/SRP: C28.1, C29.1, R47.2, U3.14 (SRP)
/SRP_BMS: C8.1, C9.1, R8.1, U1.10 (SRP)
/STAT1: J9.2, R22.2, U3.5 (STAT1)
/STAT2: R1.2, U3.9 (STAT2)
/SYSTEM: C19.1, C20.1, C21.1, C30.1, D4.1 (K), J2.1, J10.1, J10.2, J11.1, J11.2, Q9.5 (D), Q11.1 (S), Q11.2 (S), Q11.3 (S), R18.1, R43.4
/TS: C25.1, R44.1, U3.6 (TS)
/TS_BMS: R7.2, TH1.1, U1.18 (TS)
/TTC: C23.1, U3.7 (TTC)
/VBUS: C11.2, C12.1, D1.2 (A), D2.1 (K), J6.A4 (VBUS), J6.A9 (VBUS), J6.B4 (VBUS), J6.B9 (VBUS), Q6.1 (S), Q6.2 (S), Q6.3 (S), R24.1, R28.1, U2.24 (VDD)
/VBUS_EN_SNK: R29.2, U2.16 (VBUS_EN_SNK)
/VC0: C5.2, R5.2, U1.8 (VC0)
/VC1: C3.2, C4.1, R4.2, U1.7 (VC1)
/VC2: C2.2, C3.1, R3.2, U1.6 (VC2)
/VC3: C2.1, R2.2, U1.3 (VC5), U1.4 (VC4), U1.5 (VC3)
/VCC: C22.1, R38.2, U3.24 (VCC)
/VDD: C6.1, R6.1, R13.1, U1.1 (VDD)
/VFB: C32.2, R49.2, R50.1, U3.12 (VFB)
/VREF: C24.1, R34.1, R39.1, R41.1, R45.1, U3.4 (CE), U3.10 (VREF)
/VSNK: C16.1, D10.2 (A), Q6.5 (D), R20.1
/VS_DISCH: R25.2, U2.18 (VBUS_VS_DISCH)
/VTB: R7.1, U1.19 (VTB)
/~PG: R23.2, U3.8 (*PG)
GND: C11.1, C12.2, C13.2, C14.2, C15.2, C17.2, C19.2, C20.2, C21.2, C22.2, C23.2, C24.2, C25.2, C26.2, C28.2, C31.2, C33.2, C34.2, C35.2, D2.2 (A), D3.2 (A), D4.2 (A), D11.3 (A), H1.1, H2.1, H3.1, H4.1, J1.4, J2.2, J2.3, J5.2, J5.3, J6.A1 (GND), J6.A12 (GND), J6.B1 (GND), J6.B12 (GND), J8.1, J9.1, J10.3, J10.4, J11.3, J11.4, Q3.1 (S), Q3.2 (S), Q3.3 (S), Q4.1 (G), Q10.1 (S), Q10.2 (S), Q10.3 (S), R16.2, R17.2, R21.2, R35.2, R40.2, R42.2, R46.2, R50.2, TH3.2, U2.10 (GND), U2.12 (ADDR0), U2.13 (ADDR1), U2.25 (GND), U3.17 (GND), U3.25 (EPAD)
unnamed: C16.2, R30.2
unnamed: C15.1, D1.1 (K), R24.2, R25.1
unnamed: D5.1 (K), R23.1
unnamed: D6.1 (K), R22.1
unnamed: D7.1 (K), R1.1
unnamed: D9.2 (A), J5.1
unnamed: L1.1, R47.1
unnamed: Q1.5 (D), Q3.5 (D)
unnamed: Q1.4 (G), R11.1, R12.2
unnamed: Q1.1 (S), Q1.2 (S), Q1.3 (S), R19.1
unnamed: Q2.3 (D), Q4.3 (D)
unnamed: Q3.4 (G), R15.2, R17.1
unnamed: Q4.2 (S), R15.1
unnamed: Q6.4 (G), R28.2, R29.1, R30.1
unnamed: C1.2, Q7.4 (G), Q8.4 (G), R36.2, R37.1
unnamed: Q8.5 (D), R43.1
unnamed: C30.2, Q11.4 (G), R18.2, R48.2
unnamed: R10.2, R19.2
unnamed: R8.2, R19.3

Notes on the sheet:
Li-Ion Charger
I_chg*20*R_sr=V_iset1 | 0.32V -> 2A I_term*100*R_sr=V_iset2 | 0.16V -> 0.1A I_AC*20*R_ac=V_acset | 0.32V -> 2A
USB-PD
OCDP Resistor = 750k: OCD1 Delay = 1.42s OCD2 Delay = 0.7s
I2C ADR: 0101000
OCC | OCD1/2 | SCD 60mV | 60mV | 120mV 8A ±20% | 8A ±20% | 16A ±20%
BMS
